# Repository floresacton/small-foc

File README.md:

# small-foc
ST Spin G4 based FOC controller

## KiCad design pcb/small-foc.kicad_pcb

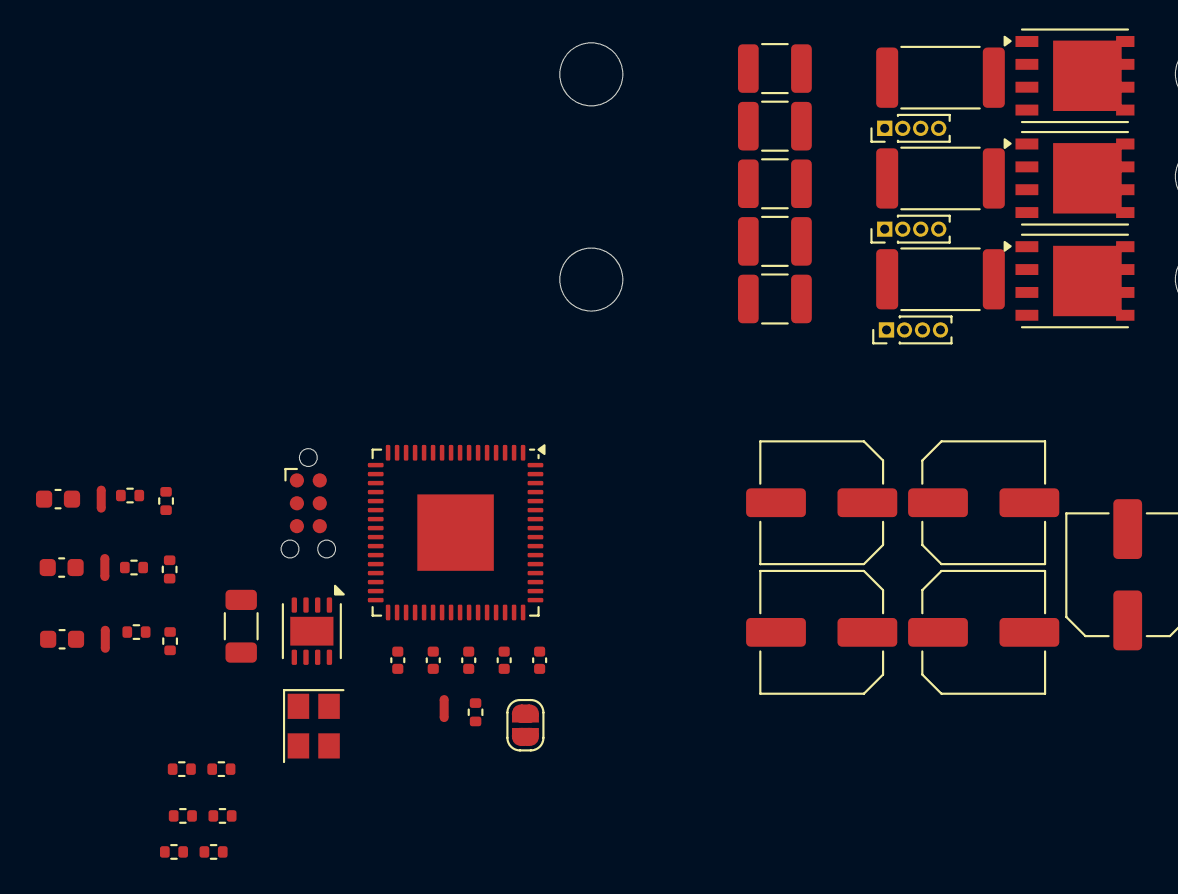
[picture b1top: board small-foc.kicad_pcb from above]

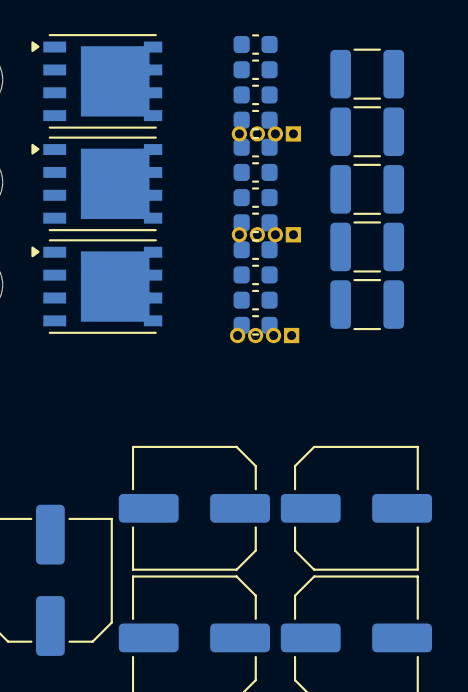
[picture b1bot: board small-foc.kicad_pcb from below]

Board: 4 copper layers, 40 parts (3 on the bottom side), 44 nets, no tracks yet.

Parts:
C5, C15, C17: 100n; C_0402_1005Metric
C11, C12, C13: 470n; C_0603_1608Metric
C14, C16: 12p; C_0402_1005Metric
J1: Conn_ARM_SWD_TagConnect_TC2030-NL; Tag-Connect_TC2030-IDC-NL_2x03_P1.27mm_Vertical
JP1: SolderJumper_2_Open; SolderJumper-2_P1.3mm_Open_RoundedPad1.0x1.5mm
NT2, NT3, NT4, NT5: NetTie_2; NetTie-2_SMD_Pad0.5mm
Q1, Q2, Q3, Q4, Q5, Q6: NTMFS6H801NLT1G; PowerPAK_SO-8_Single
R9, R10, R14, R15, R19, R20: 10R; R_0402_1005Metric
R11, R16, R21: 1m; R_2512_6332Metric
R12, R17, R22: 100R; R_0402_1005Metric
R13, R18, R23: 3k3; R_0402_1005Metric
R24: 1k; R_0402_1005Metric
R25: 120; R_1206_3216Metric
U1: STSPIN32G4; Texas_RGC0064B_VQFN-64-1EP_9x9mm_P0.5mm_EP4.25x4.25mm
U2: TJA1044GTK/3; HVSON-8-1EP_3x3mm_P0.65mm_EP1.6x2.4mm
Y1: 16MHz; Crystal_SMD_3225-4Pin_3.2x2.5mm

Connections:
+3V3: C17.1, J1.1 (VCC), U1.1 (REG3/VDD), U1.2 (VBAT), U2.5 (VIO)
+3V3A: C5.1, R13.1, R18.1, R23.1, U1.26 (VREF+), U1.27 (VDDA)
+5V: C15.1, U1.64 (REGIN), U2.3 (VCC)
/BSTA: C11.1, U1.41 (BOOT1)
/BSTB: C12.1, U1.38 (BOOT2)
/BSTC: C13.1, U1.35 (BOOT3)
/CANH: R25.1, U2.7 (CANH)
/CANL: JP1.1 (A), U2.6 (CANL)
/CNRX: U1.47 (PA11), U2.4 (RXD)
/CNTX: U1.48 (PA12), U2.1 (TXD)
/INHA: R9.1, U1.43 (GHS1)
/INHB: R14.1, U1.40 (GHS2)
/INHC: R19.1, U1.37 (GHS3)
/INLA: R10.1, U1.29 (GLS1)
/INLB: R15.1, U1.30 (GLS2)
/INLC: R20.1, U1.31 (GLS3)
/NRST: J1.3 (~RESET), U1.8 (PG10)
/PHA: C11.2, Q1.1 (S), Q1.2 (S), Q1.3 (S), Q2.5 (D), U1.42 (OUT1)
/PHB: C12.2, Q3.1 (S), Q3.2 (S), Q3.3 (S), Q4.5 (D), U1.39 (OUT2)
/PHC: C13.2, Q5.1 (S), Q5.2 (S), Q5.3 (S), Q6.5 (D), U1.36 (OUT3)
/SNSHA: R12.2, R13.2, U1.14 (PA1)
/SNSHB: R17.2, R18.2, U1.20 (PA7)
/SNSHC: R22.2, R23.2, U1.23 (PB0)
/SNSLA: NT3.2, U1.16 (PA3)
/SNSLB: NT4.2, U1.18 (PA5)
/SNSLC: NT5.2, U1.25 (PB2)
/SWCLK: J1.4 (SWCLK), U1.50 (PA14)
/SWDIO: J1.2 (SWDIO), U1.49 (PA13)
/XTALI: C14.2, U1.6 (PF0), Y1.1
/XTALO: R24.2, U1.7 (PF1)
/XTALR: C16.2, R24.1, Y1.3
GND: C5.2, C14.1, C15.2, C16.1, C17.2, J1.5 (GND), NT2.2, U1.59 (PB8), U1.65 (EPAD), U2.2 (GND), U2.9 (EPAD), Y1.2, Y1.4
GNDPWR: NT2.1, NT3.1, NT4.1, NT5.1, R11.2, R16.2, R21.2, U1.32 (PGND)
unnamed: JP1.2 (B), R25.2
unnamed: Q1.4 (G), R9.2
unnamed: Q2.4 (G), R10.2
unnamed: Q2.1 (S), Q2.2 (S), Q2.3 (S), R11.1, R12.1
unnamed: Q3.4 (G), R14.2
unnamed: Q4.4 (G), R15.2
unnamed: Q4.1 (S), Q4.2 (S), Q4.3 (S), R16.1, R17.1
unnamed: Q5.4 (G), R19.2
unnamed: Q6.4 (G), R20.2
unnamed: Q6.1 (S), Q6.2 (S), Q6.3 (S), R21.1, R22.1
VDD: Q1.5 (D), Q3.5 (D), Q5.5 (D)

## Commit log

2025-01-22 Save
2025-01-24 Fix filenames
